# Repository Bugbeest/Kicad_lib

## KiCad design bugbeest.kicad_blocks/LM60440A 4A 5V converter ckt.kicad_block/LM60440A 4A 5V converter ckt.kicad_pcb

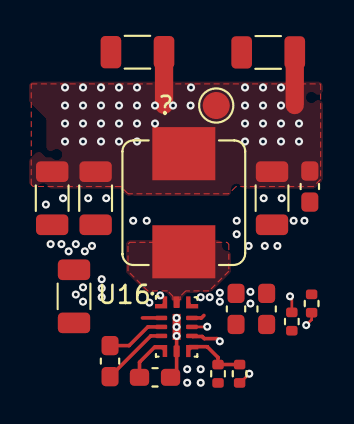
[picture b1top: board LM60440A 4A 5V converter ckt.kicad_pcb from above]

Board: 4 copper layers, 18 parts (0 on the bottom side), 10 nets.

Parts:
?: 24.9k; R_0402_1005Metric
?#2: 100k; R_0402_1005Metric
?#3: TestPoint; TestPoint_Pad_D1.5mm
C75: 4.7uF; C_1206_3216Metric
C76, C77: 0.22uF; C_0603_1608Metric_Pad1.08x0.95mm_HandSolder
C78, C79, C85: 0.1uF; C_0603_1608Metric_Pad1.08x0.95mm_HandSolder
C80: 47uF; C_1206_3216Metric
C81, C82, C83, C84: 22uF; C_1206_3216Metric
L6: 15uH; L_Bourns_SRP7028A_7.3x6.6mm
R94, R95: 10k; R_0402_1005Metric
U16: LM60440A-Q1; TI_WQFN-13_P0.5_EP

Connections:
+5V: ?#2.2, ?#3.1, C80.1, C81.1, C82.1, C83.1, C84.1, C85.1, L6.2
/Compute/PGOOD: R95.1, U16.8 (PG)
/power/sw: L6.1, U16.12 (SW)
GND: ?.1, C75.2, C76.2, C77.2, C78.2, C80.2, C81.2, C82.2, C83.2, C84.2, C85.2, U16.1 (PGND), U16.6 (AGND), U16.11 (PGND), U16.13 (DAP)
unnamed: C79.2, U16.3 (SW)
unnamed: C79.1, U16.4 (BOOT)
unnamed: R94.1, U16.9 (EN)
unnamed: ?.2, ?#2.1, U16.7 (FB)
unnamed: C78.1, U16.5 (VCC)
V_Supp: C75.1, C76.1, C77.1, R94.2, U16.2 (VIN), U16.10 (VIN)

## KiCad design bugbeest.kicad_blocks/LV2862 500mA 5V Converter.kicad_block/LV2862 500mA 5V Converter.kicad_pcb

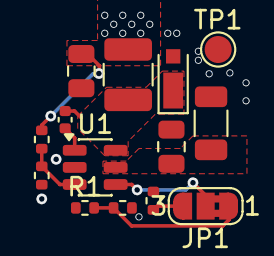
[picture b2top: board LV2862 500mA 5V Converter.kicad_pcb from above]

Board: 4 copper layers, 14 parts (0 on the bottom side), 9 nets.

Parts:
C1: 4.7uF; C_1206_3216Metric
C2: 0.22uF; C_0805_2012Metric
C3: 0.1uF; C_0402_1005Metric
C4: 10uF; C_0805_2012Metric
D1: MSS1P3L-M3/89A; D_MicroSMP_LargeCathode
JP1: Jumper_2_Small_Open; SolderJumper-3_P1.3mm_Bridged2Bar12_RoundedPad1.0x1.5mm_Num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
L1: 15uH; L_1210_3225Metric
R1: 100; R_0402_1005Metric
R2, R3: 100k; R_0402_1005Metric
R4: 33.2K; R_0402_1005Metric
R5: 10k; R_0402_1005Metric
TP1: TestPoint; TestPoint_Pad_D1.5mm
U1: LV2862YDDC; SOT-23-6

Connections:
/sw: C3.2, D1.1 (K), L1.1, U1.6 (SW)
unnamed: C4.1, L1.2, R4.2, TP1.1 (1_1)
unnamed: C1.2, C2.2, C4.2, D1.2 (A), R3.1, R5.1, U1.2 (GND)
unnamed: JP1.1 (A), R1.2, R3.2
unnamed: JP1.3 (B), R2.1
unnamed: JP1.2 (C), U1.4 (~SHDN)
unnamed: C3.1, U1.1 (CB)
unnamed: R4.1, R5.2, U1.3 (FB)
unnamed: C1.1, C2.1, R2.2, U1.5 (VIN)

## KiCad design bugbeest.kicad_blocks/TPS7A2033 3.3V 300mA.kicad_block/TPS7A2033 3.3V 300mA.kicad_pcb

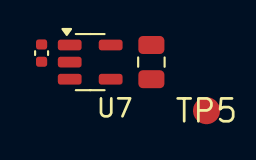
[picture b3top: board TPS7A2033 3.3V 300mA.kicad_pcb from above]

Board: 4 copper layers, 4 parts (0 on the bottom side), 3 nets, no tracks yet.

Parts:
C37: 0.1uF; C_0402_1005Metric
C39: 10uF; C_0805_2012Metric
TP5: (no value)
U7: AP2127K-3.3; SOT-23-5

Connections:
+3.3V: C39.1, TP5.1, U7.5 (VOUT)
+5V: C37.1, U7.1 (VIN), U7.3 (EN)
GND: C37.2, C39.2, U7.2 (GND)

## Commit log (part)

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2024-06-02 committing current state
2025-02-28 converted to modern library format, added SN74AHC125PWR
2025-03-01 added TVS diode array
2025-03-05 updated something
2025-03-06 added DC-DC converter
2025-03-06 added footprint for DC-DC converter
2025-03-06 added cmc
2025-03-12 added TCA6408 IO expander
2025-03-12 added 3D model for IO expander
2025-03-12 added PD-40V
2025-03-13 added several connectors
2025-03-14 added some connectors
2025-03-15 added connector
2025-03-16 added CANbus transciever
2025-03-18 component models and Qwiic decals added
2025-04-21 added cmc footprint
2025-05-13 added e-fuse
2025-05-13 adding some connectors
2025-10-21 added hand solderable APA102-2020 footprint
